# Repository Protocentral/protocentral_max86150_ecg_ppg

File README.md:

Protocentral MAX86150 PPG & ECG sensor
======================================

## Don't have one? [Buy it here](https://protocentral.com/product/protocentral-max86150-ppg-and-ecg-breakout-with-qwiic-v2/)

The MAX86150 breakout board is an all in one module that supports a trio of functions for human vitals monitoring. It integrates the Pulse oximeter (SPO2), Electrocardiogram (ECG) and Heart rate sensor module into this breakout board. In more scientific terms, it is integrated with the Photoplethysmogram and Electrocardiogram biosensor module.

What makes this breakout exceptional is that it is the only touch-based module available to detect both SPO2 as well as ECG. The breakout board allows Qwiic connect as well as breadboard mounting with the provided pins. It is designed to accommodate both the ECG touchpad and the external ECG stereo connector. However, they are configured in a way that they function in an exclusive manner when one mode is active the other remains passive. Any microcontroller such as Arduino is compatible and the communication protocol used is I2C to stream data. With all the above features, this board is best suited for any Mobile health monitoring as well as in wearable devices.

## Hardware Setup

Connection with the Arduino board is as follows:
 
 |MAX86150 pin label| Arduino Connection  |Pin Function      |
 |:-----------------: |:---------------------:|:------------------:|
 | SDA              | SDA                  |  Serial Data     |
 | SCL              | SCL                  |  Serial Clock    |
 | 5V               | 5V                  |  Power           |
 | GND              | GND                 |  GND             |
 | INT              | --                  |  Interrupt            |

## Visualizing Output

## For further details, refer [the documentation on MAX86150 PPG & ECG sensor](https://docs.protocentral.com/getting-started-with-max86150/)

License Information
===================

This product is open source! Both, our hardware and software are open source and licensed under the following licenses:

Hardware
---------

**All hardware is released under the [CERN-OHL-P v2](https://ohwr.org/cern_ohl_p_v2.txt)** license.

Copyright CERN 2020.

This source describes Open Hardware and is licensed under the CERN-OHL-P v2.

You may redistribute and modify this documentation and make products
using it under the terms of the CERN-OHL-P v2 (https:/cern.ch/cern-ohl).
This documentation is distributed WITHOUT ANY EXPRESS OR IMPLIED
WARRANTY, INCLUDING OF MERCHANTABILITY, SATISFACTORY QUALITY
AND FITNESS FOR A PARTICULAR PURPOSE. Please see the CERN-OHL-P v2
for applicable conditions

Software
--------

**All software is released under the MIT License(http://opensource.org/licenses/MIT).**

THE SOFTWARE IS PROVIDED "AS IS", WITHOUT WARRANTY OF ANY KIND, EXPRESS OR IMPLIED, INCLUDING BUT NOT LIMITED TO THE WARRANTIES OF MERCHANTABILITY, FITNESS FOR A PARTICULAR PURPOSE AND NONINFRINGEMENT. IN NO EVENT SHALL THE AUTHORS OR COPYRIGHT HOLDERS BE LIABLE FOR ANY CLAIM, DAMAGES OR OTHER LIABILITY, WHETHER IN AN ACTION OF CONTRACT, TORT OR OTHERWISE, ARISING FROM, OUT OF OR IN CONNECTION WITH THE SOFTWARE OR THE USE OR OTHER DEALINGS IN THE SOFTWARE.

Documentation
-------------
**All documentation is released under [Creative Commons Share-alike 4.0 International](http://creativecommons.org/licenses/by-sa/4.0/).**

You are free to:

* Share — copy and redistribute the material in any medium or format
* Adapt — remix, transform, and build upon the material for any purpose, even commercially.
The licensor cannot revoke these freedoms as long as you follow the license terms.

Under the following terms:

* Attribution — You must give appropriate credit, provide a link to the license, and indicate if changes were made. You may do so in any reasonable manner, but not in any way that suggests the licensor endorses you or your use.
* ShareAlike — If you remix, transform, or build upon the material, you must distribute your contributions under the same license as the original.

Please check [*LICENSE.md*](LICENSE.md) for detailed license descriptions.

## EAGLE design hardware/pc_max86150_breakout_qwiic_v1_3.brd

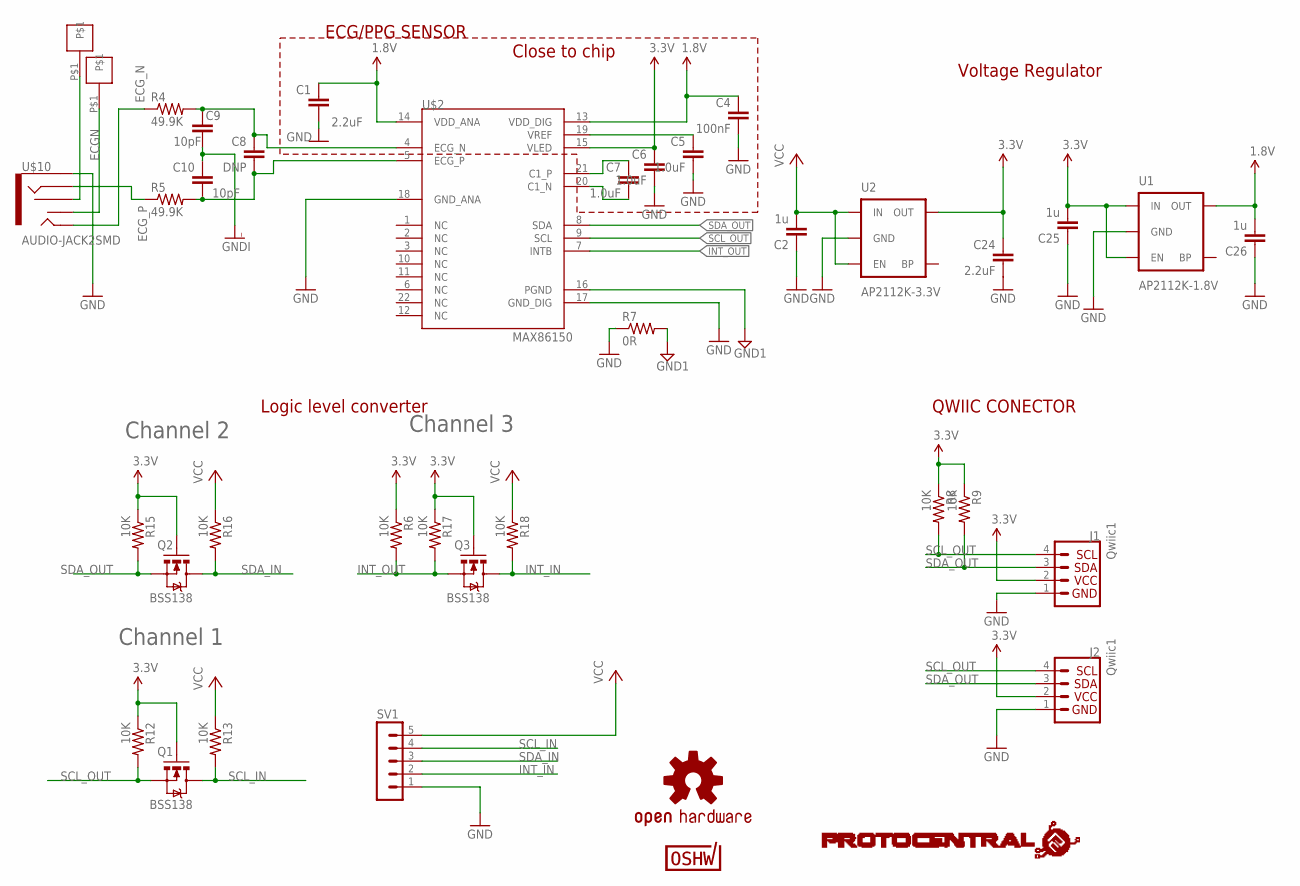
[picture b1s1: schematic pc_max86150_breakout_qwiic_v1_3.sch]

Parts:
C1: 2.2uF; 0402
C2, C25, C26: 1u; C0402
C4: 100nF; 0402
C5, C6, C7: 1.0uF; 0402
C8: DNP; 0402
C9, C10: 10pF; 0402
C24: 2.2uF; C0402
J1, J2: Qwiic1; 1X04_1MM_RA
Q1, Q2, Q3: BSS138; SOT23-3
R4, R5: 49.9K; 0402-RES
R6, R8, R9, R12, R13, R15, R16, R17, R18: 10K; 0402-RES
R7: 0R; 0402-RES
SV1: MA05-1
U1: AP2112K-1.8V; SOT23-5
U2: AP2112K-3.3V; SOT23-5
U$2: MAX86150
U$3: PROTY_LOGO_WITH_TEXT; PROTY_WITH_TEXT
U$4, U$13: ECG_PAD; ECG_PAD1
U$10: AUDIO-JACK2SMD; AUDIO-JACK-3.5MM-SMD
U$12: OSHW-LOGOM; OSHW-LOGO-M
U$17: CERT-SMALL; CERT-SMALL-SILK

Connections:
1.8V: C1.1, C4.1, C26.2, U1.5 (OUT), U$2.13 (VDD_DIG), U$2.14 (VDD_ANA)
3.3V: C6.1, C24.1, C25.2, J1.2, J2.2, Q1.1 (G), Q2.1 (G), Q3.1 (G), R6.1, R8.1, R9.1, R12.1, R15.1, R17.1, U1.1 (IN), U1.3 (EN), U2.5 (OUT), U$2.15 (VLED)
@: U$4.P$1, U$10.RSH
ECGN: U$10.TSH, U$13.P$1
ECG_N: R4.1, U$10.TIP
ECG_P: R5.1, U$10.RING
GND: C1.2, C2.1, C4.2, C5.2, C6.2, C24.2, C25.1, C26.1, J1.1, J2.1, R7.1, SV1.1, U1.2 (GND), U2.2 (GND), U$2.17 (GND_DIG), U$2.18 (GND_ANA), U$10.SLEEVE
GND1: R7.2, U$2.16 (PGND)
GNDI: C9.2, C10.1
INT_IN: Q3.3 (D), R18.2, SV1.2
INT_OUT: Q3.2 (S), R6.2, R17.2, U$2.7 (INTB)
unnamed: C7.1, U$2.21 (C1_P)
unnamed: C7.2, U$2.20 (C1_N)
unnamed: C8.1, C9.1, R4.2, U$2.4 (ECG_N)
unnamed: C5.1, U$2.19 (VREF)
unnamed: C8.2, C10.2, R5.2, U$2.5 (ECG_P)
SCL_IN: Q1.3 (D), R13.2, SV1.4
SCL_OUT: J1.4, J2.4, Q1.2 (S), R8.2, R12.2, U$2.9 (SCL)
SDA_IN: Q2.3 (D), R16.2, SV1.3
SDA_OUT: J1.3, J2.3, Q2.2 (S), R9.2, R15.2, U$2.8 (SDA)
VCC: C2.2, R13.1, R16.1, R18.1, SV1.5, U2.1 (IN), U2.3 (EN)

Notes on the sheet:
Channel 1
Channel 2
Channel 3
Voltage Regulator
ECG/PPG SENSOR
Logic level converter
QWIIC CONECTOR
Close to chip

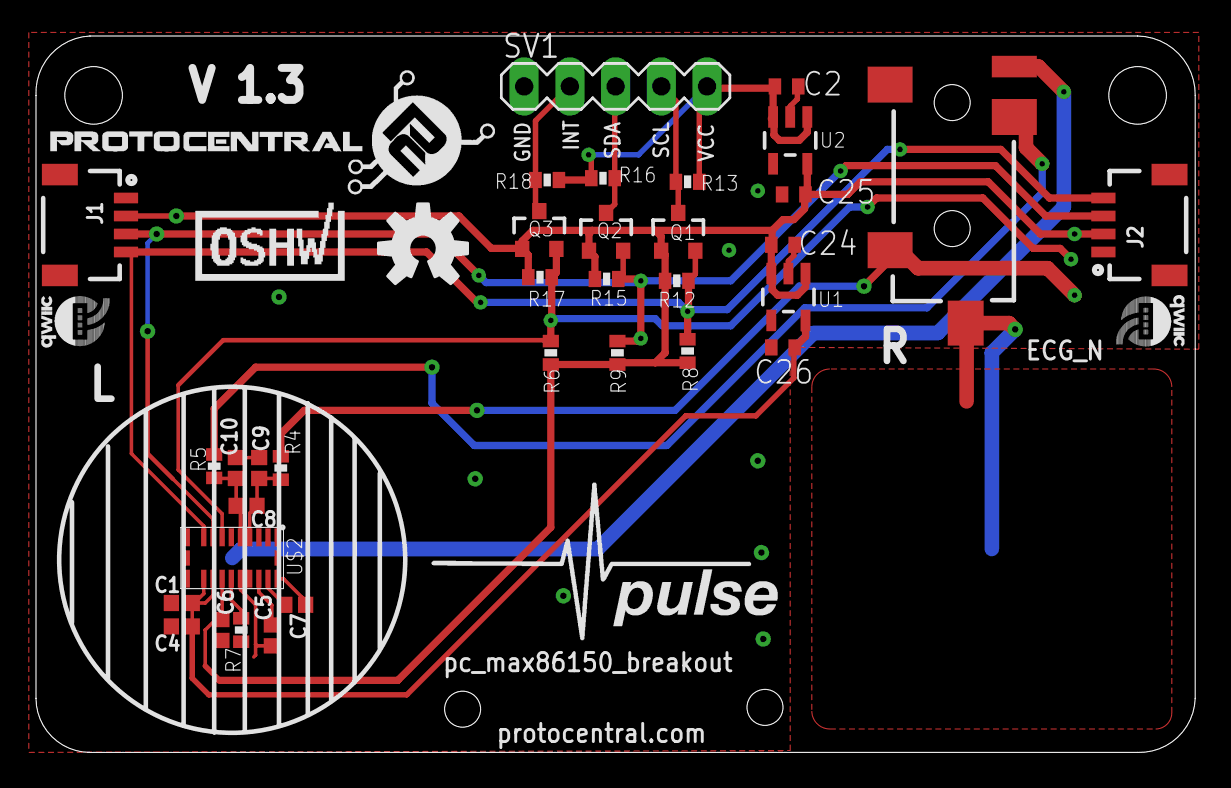
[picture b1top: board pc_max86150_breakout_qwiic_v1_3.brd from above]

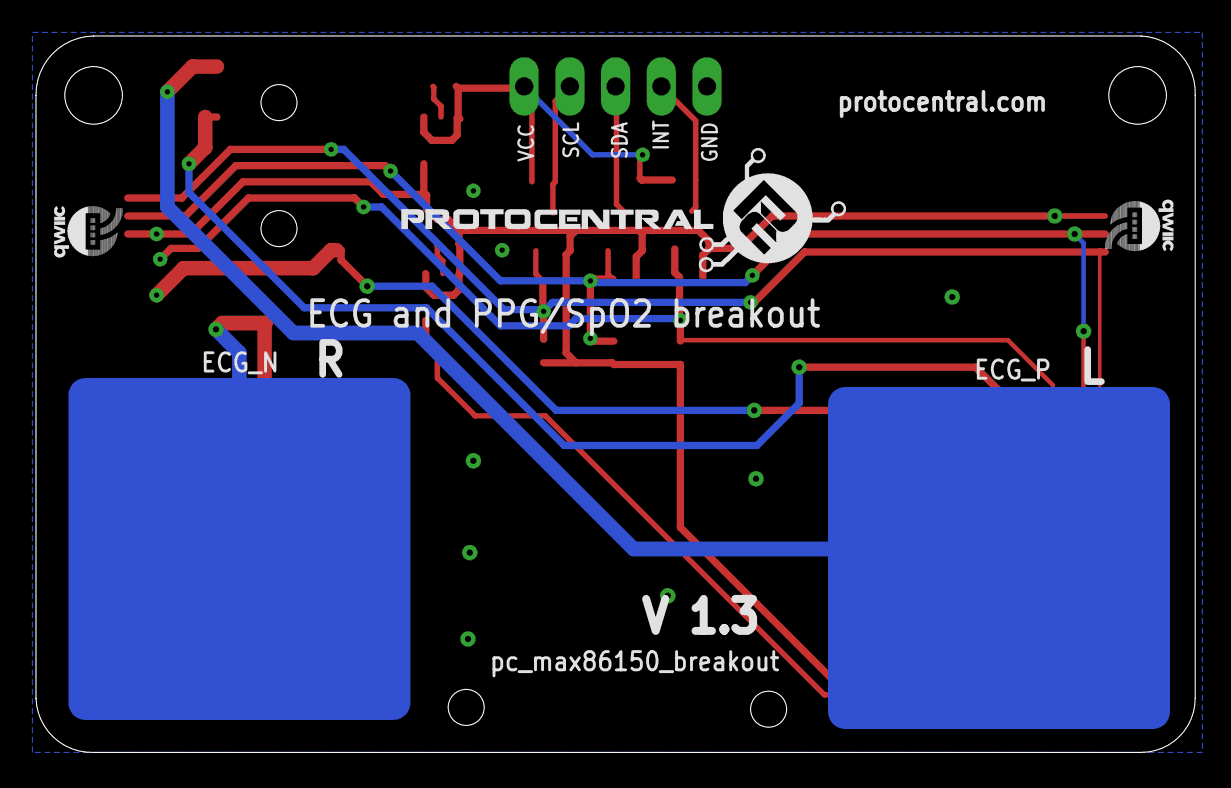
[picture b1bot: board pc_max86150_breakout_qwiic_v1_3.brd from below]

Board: 4 copper layers, 64.4 x 39.8 mm, 45 parts (5 on the bottom side), 21 nets.

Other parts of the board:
U$1: PULSE
U$6, U$9, U$11, U$59: QWIIC#LABEL#FULL#M#PNG
U$7: PROTY_LOGO_WITH_TEXT; PROTY_WITH_TEXT

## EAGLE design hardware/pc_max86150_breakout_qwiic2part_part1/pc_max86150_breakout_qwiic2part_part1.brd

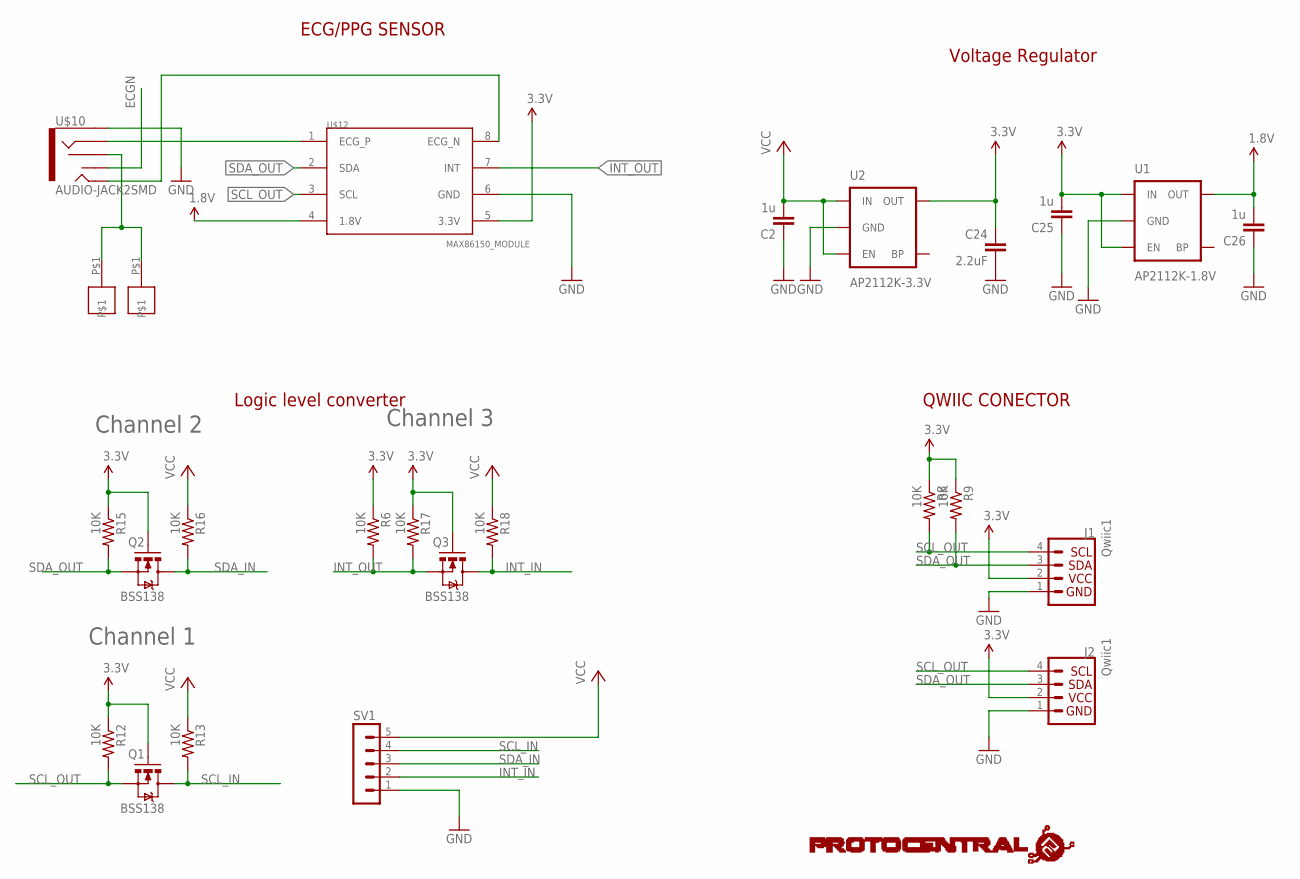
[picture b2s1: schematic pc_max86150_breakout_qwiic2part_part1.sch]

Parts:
C2, C25, C26: 1u; C0402
C24: 2.2uF; C0402
J1, J2: Qwiic1; 1X04_1MM_RA
Q1, Q2, Q3: BSS138; SOT23-3
R6, R8, R9, R12, R13, R15, R16, R17, R18: 10K; 0402-RES
SV1: MA05-1
U1: AP2112K-1.8V; SOT23-5
U2: AP2112K-3.3V; SOT23-5
U$3: PROTY_LOGO_WITH_TEXT; PROTY_WITH_TEXT
U$4, U$13: ECG_PAD; ECG_PAD1
U$10: AUDIO-JACK2SMD; AUDIO-JACK-3.5MM-SMD
U$12: MAX86150_MODULE

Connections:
1.8V: C26.2, U1.5 (OUT), U$12.4 (1.8V)
3.3V: C24.1, C25.2, J1.2, J2.2, Q1.1 (G), Q2.1 (G), Q3.1 (G), R6.1, R8.1, R9.1, R12.1, R15.1, R17.1, U1.1 (IN), U1.3 (EN), U2.5 (OUT), U$12.5 (3.3V)
ECGN: U$10.TSH
GND: C2.1, C24.2, C25.1, C26.1, J1.1, J2.1, SV1.1, U1.2 (GND), U2.2 (GND), U$10.SLEEVE, U$12.6 (GND)
INT_IN: Q3.3 (D), R18.2, SV1.2
INT_OUT: Q3.2 (S), R6.2, R17.2, U$12.7 (INT)
unnamed: U$10.TIP, U$12.8 (ECG_N)
unnamed: U$10.RING, U$12.1 (ECG_P)
unnamed: U$4.P$1, U$10.RSH, U$13.P$1
SCL_IN: Q1.3 (D), R13.2, SV1.4
SCL_OUT: J1.4, J2.4, Q1.2 (S), R8.2, R12.2, U$12.3 (SCL)
SDA_IN: Q2.3 (D), R16.2, SV1.3
SDA_OUT: J1.3, J2.3, Q2.2 (S), R9.2, R15.2, U$12.2 (SDA)
VCC: C2.2, R13.1, R16.1, R18.1, SV1.5, U2.1 (IN), U2.3 (EN)

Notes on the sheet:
Channel 1
Channel 2
Channel 3
Voltage Regulator
ECG/PPG SENSOR
Logic level converter
QWIIC CONECTOR

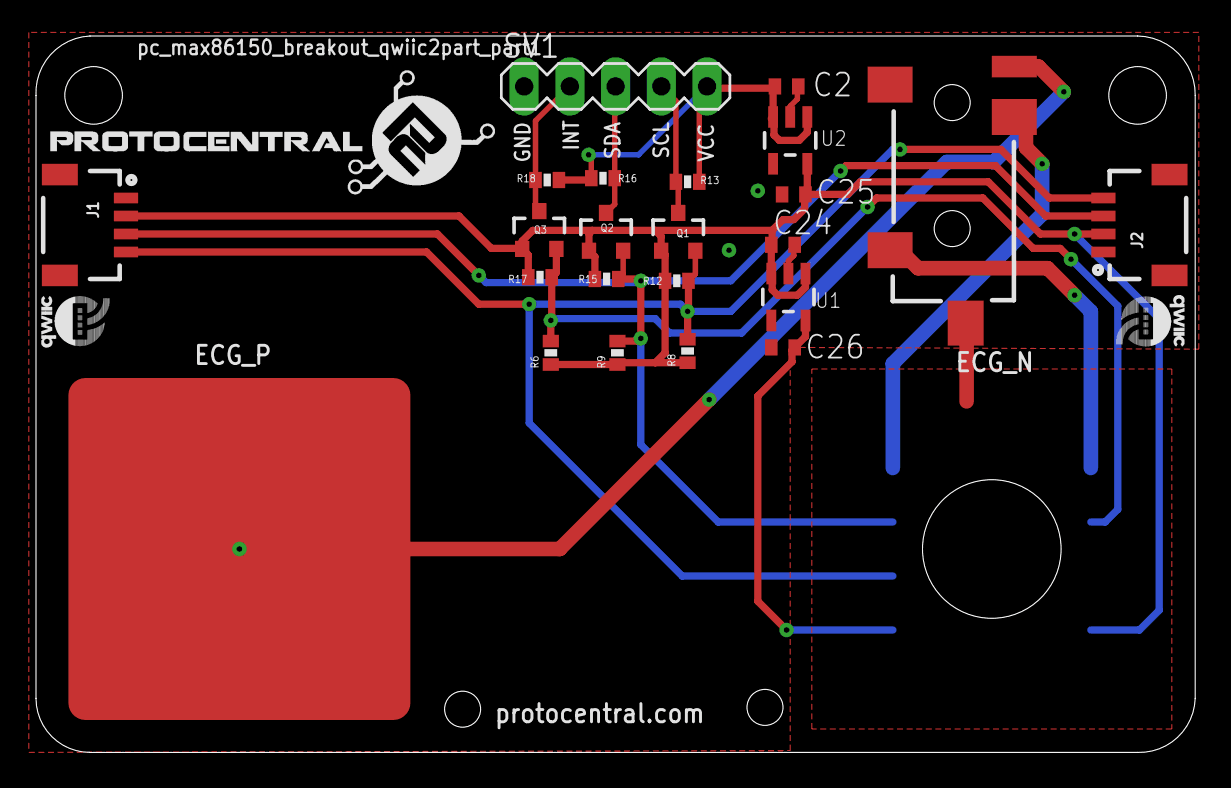
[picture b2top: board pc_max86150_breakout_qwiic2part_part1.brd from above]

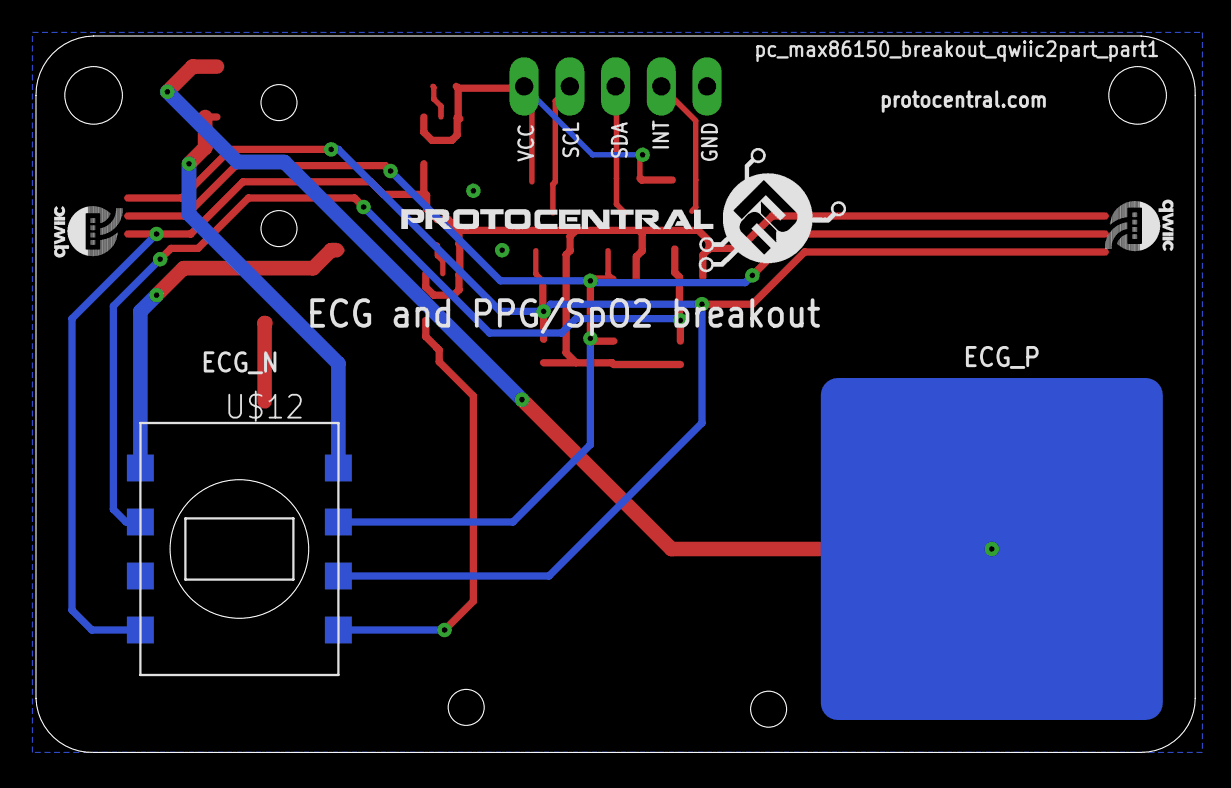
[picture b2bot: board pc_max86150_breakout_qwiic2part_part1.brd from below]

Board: 4 copper layers, 64.4 x 39.8 mm, 31 parts (4 on the bottom side), 13 nets.

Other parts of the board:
U$6, U$9, U$11, U$59: QWIIC#LABEL#FULL#M#PNG
U$7: PROTY_LOGO_WITH_TEXT; PROTY_WITH_TEXT

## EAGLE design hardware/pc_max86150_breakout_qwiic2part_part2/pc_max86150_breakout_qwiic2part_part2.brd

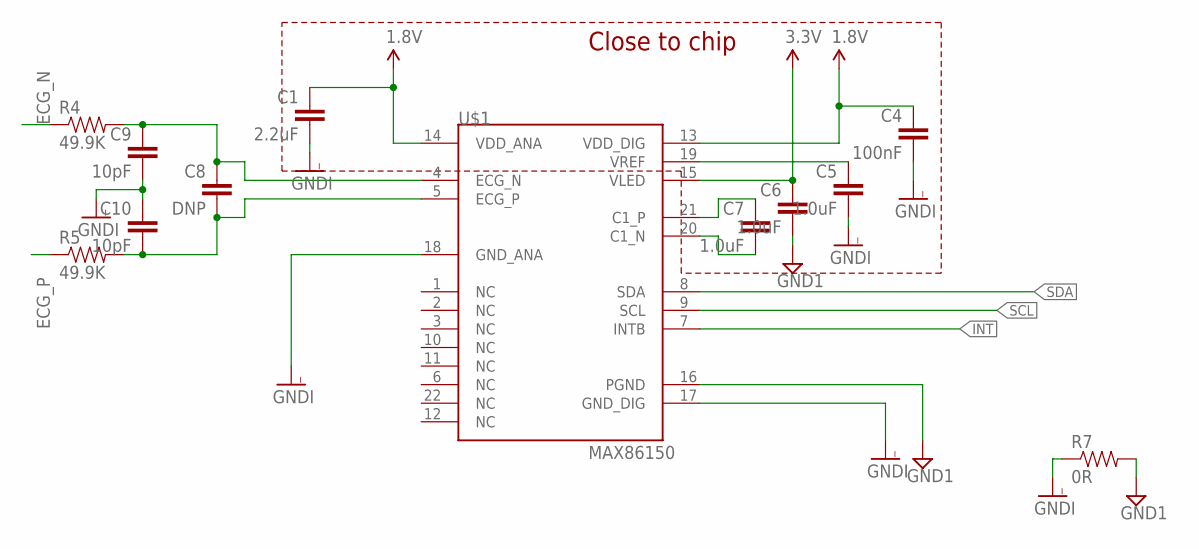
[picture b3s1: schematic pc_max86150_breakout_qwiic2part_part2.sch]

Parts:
C1: 2.2uF; 0402
C4: 100nF; 0402
C5, C6, C7: 1.0uF; 0402
C8: DNP; 0402
C9, C10: 10pF; 0402
R4, R5: 49.9K; 0402-RES
R7: 0R; 0402-RES
U$1: MAX86150

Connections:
1.8V: C1.1, C4.1, U$1.13 (VDD_DIG), U$1.14 (VDD_ANA)
3.3V: C6.1, U$1.15 (VLED)
ECG_N: R4.1
ECG_P: R5.1
GND1: C6.2, R7.2, U$1.16 (PGND)
GNDI: C1.2, C4.2, C5.2, C9.2, C10.1, R7.1, U$1.17 (GND_DIG), U$1.18 (GND_ANA)
INT: U$1.7 (INTB)
unnamed: C7.1, U$1.21 (C1_P)
unnamed: C7.2, U$1.20 (C1_N)
unnamed: C8.1, C9.1, R4.2, U$1.4 (ECG_N)
unnamed: C5.1, U$1.19 (VREF)
unnamed: C8.2, C10.2, R5.2, U$1.5 (ECG_P)
SCL: U$1.9 (SCL)
SDA: U$1.8 (SDA)

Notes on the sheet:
Close to chip

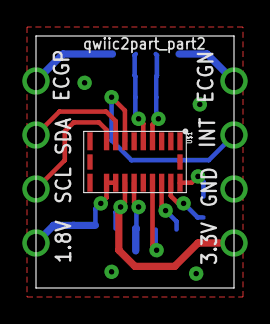
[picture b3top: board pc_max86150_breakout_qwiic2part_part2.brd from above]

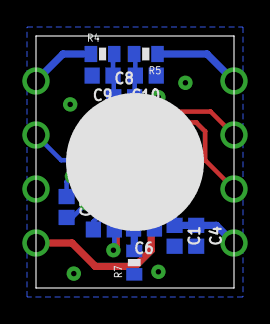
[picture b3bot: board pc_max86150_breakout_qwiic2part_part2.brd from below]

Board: 4 copper layers, 11.0 x 14.0 mm, 12 parts (11 on the bottom side), 9 nets.

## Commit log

2019-04-11 Updated readme, removed keywords
2019-04-24 ECG functionality working
2019-04-24 Bump version number in library.properties
2019-04-25 Replaced cover photo, example 1 correction
2019-05-06 Added hardware files
2019-05-08 Added example 3, ECG and PPG combined
2020-03-12 Fix include of max86150.h
    The file is named max86150.h (lower case letters), but
    it was included as MAX86150.h, causing build to fail on
    case sensitive operating systems such as Linux.
2020-12-29 added example for protocentral_openview gui
2020-12-30 fixed data len
2020-12-31 fixed datalen
2020-12-31 Updated latest hardware files
2021-01-01 v1.0.0
2021-03-26 Update License Information
2022-02-16 Add: Filter for ECG
2022-12-15 Fixed build errors on ESP32
2022-12-15 Fixed build errors with ESP32
2022-12-15 Added GH workflow
2022-12-16 Removed FIR library dependency
2023-04-10 Fixed shutdown & wakeup functions
    MAX86150_SHUTDOWN_MASK and MAX86150_SHUTDOWN definitions were incorrect (they were for max30102) which caused shutdown and wakeup functions not to work properly.
2024-11-28 readme updated, schematic extracted, workflow updated
2024-11-28 changed from v3 to v4
2024-11-28 update workflow

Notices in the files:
README.md:
CC-BY-SA-4.0
parts and their libraries:
SparkFun-Connectors: Licensing: Creative Commons ShareAlike 4.0 International - https://creativecommons.org/licenses/by-sa/4.0
